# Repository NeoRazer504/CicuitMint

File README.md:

# CircuitMint
CircuitMint is a mini keyboard made solely to make my life easier by turning the shortcuts I use most into just a single button press! It has 4 buttons and a OLED screen(mostly just to make it cooler).

## CAD

Made in Onshape using 2 custom case parts and other components off of GrabCad

## PCB

Heres my PCB design made in KiCad.

## BOM

- 1x 3d printed case
- 1x Seeed XIAO RP2040 microcontroller
- 4x MX-Style switches
- 4x LEDs
- 1x 0.91 inch OLED display
- 4x DSA keycaps
- 4x 3x16mm screws
- 4x 3x5mx4mm heatset inserts

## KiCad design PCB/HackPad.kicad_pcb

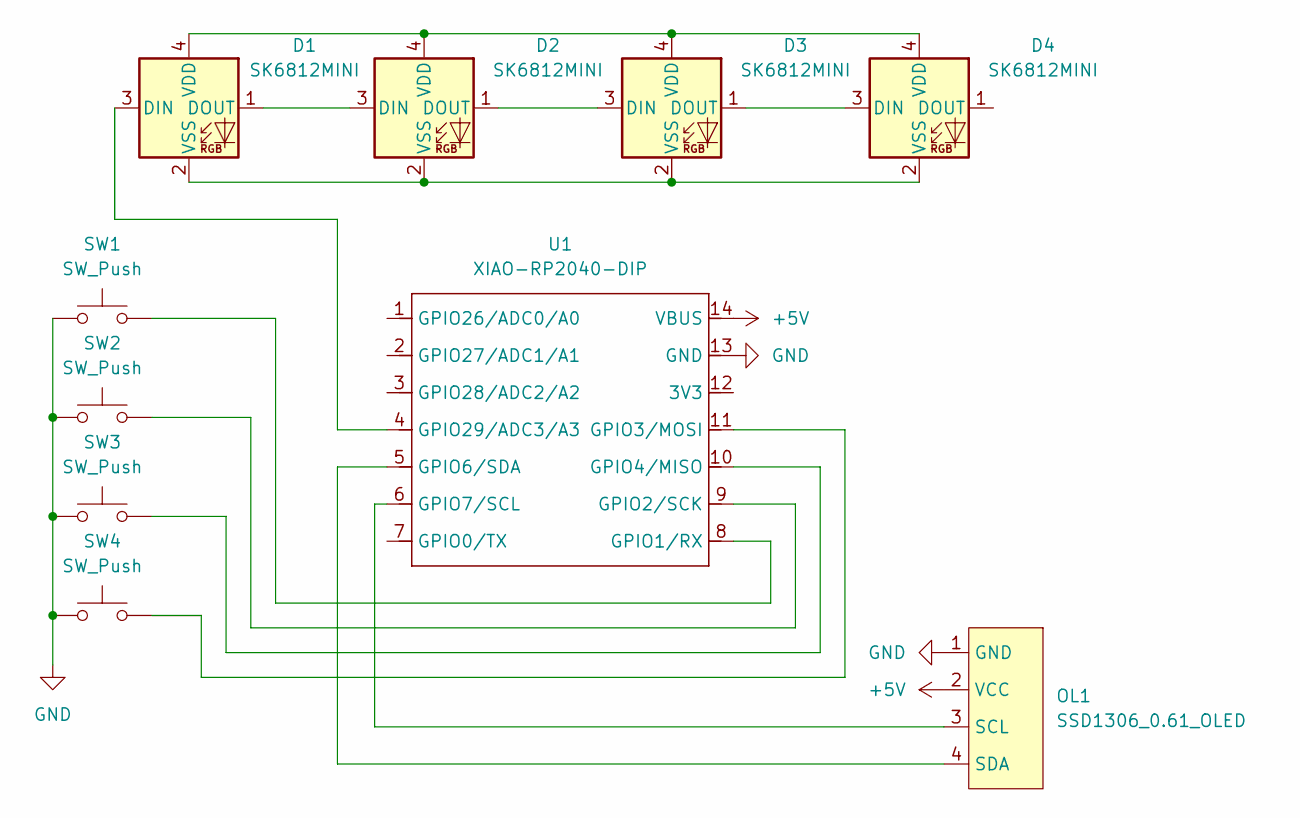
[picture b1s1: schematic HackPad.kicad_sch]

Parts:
D1, D2, D3, D4: SK6812MINI; LED_SK6812MINI_PLCC4_3.5x3.5mm_P1.75mm
OL1: SSD1306_0.61_OLED; SSD1306-0.91-OLED-4pin-128x32
SW1, SW2, SW3, SW4: SW_Push; SW_Cherry_MX_1.00u_PCB
U1: XIAO-RP2040-DIP

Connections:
+5V: OL1.2 (VCC), U1.14 (VBUS)
GND: OL1.1 (GND), SW1.1, SW2.1, SW3.1, SW4.1, U1.13 (GND)
unnamed: D1.3 (DIN), U1.4 (GPIO29/ADC3/A3)
unnamed: D1.1 (DOUT), D2.3 (DIN)
unnamed: D1.4 (VDD), D2.4 (VDD), D3.4 (VDD), D4.4 (VDD)
unnamed: D1.2 (VSS), D2.2 (VSS), D3.2 (VSS), D4.2 (VSS)
unnamed: D2.1 (DOUT), D3.3 (DIN)
unnamed: D3.1 (DOUT), D4.3 (DIN)
unnamed: OL1.3 (SCL), U1.6 (GPIO7/SCL)
unnamed: OL1.4 (SDA), U1.5 (GPIO6/SDA)
unnamed: SW1.2, U1.8 (GPIO1/RX)
unnamed: SW2.2, U1.9 (GPIO2/SCK)
unnamed: SW4.2, U1.11 (GPIO3/MOSI)
unnamed: SW3.2, U1.10 (GPIO4/MISO)

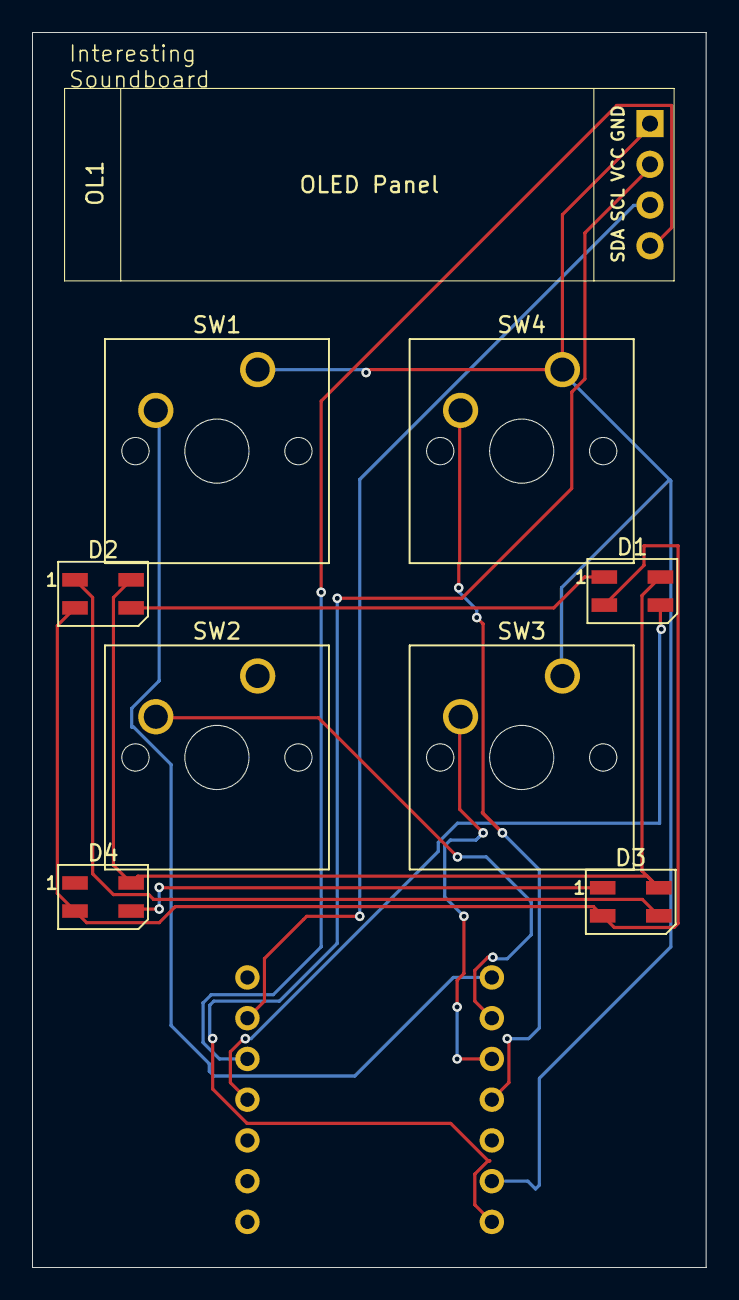
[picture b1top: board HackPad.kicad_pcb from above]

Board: 2 copper layers, 42.0 x 77.0 mm, 10 parts (1 on the bottom side), 14 nets.

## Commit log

2025-07-26 Added PCB files
2025-07-26 Made PCB folder
2025-07-26 Moved file to PCB folder
2025-07-26 Rename HackPad.kicad_pro to PCB/HackPad.kicad_pro
2025-07-26 Added firmware
2025-07-26 Added CAD
2025-07-26 Rename HackPad 1.step to CAD/CircuitMint.step
2025-07-27 Rename HackPad.zip to Production/HackPad.zip
